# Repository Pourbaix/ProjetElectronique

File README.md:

# ProjetElectronique

## Description du projet

Ceci est le repository GitHub du projet d'électronique du groupe D

## Membres du groupe 

- BORKA Mark 
- GEONET Antoine
- NECHIFOR Bogdan
- POURBAIX Michaël
- DE SOUSA FEREIRA Nuno

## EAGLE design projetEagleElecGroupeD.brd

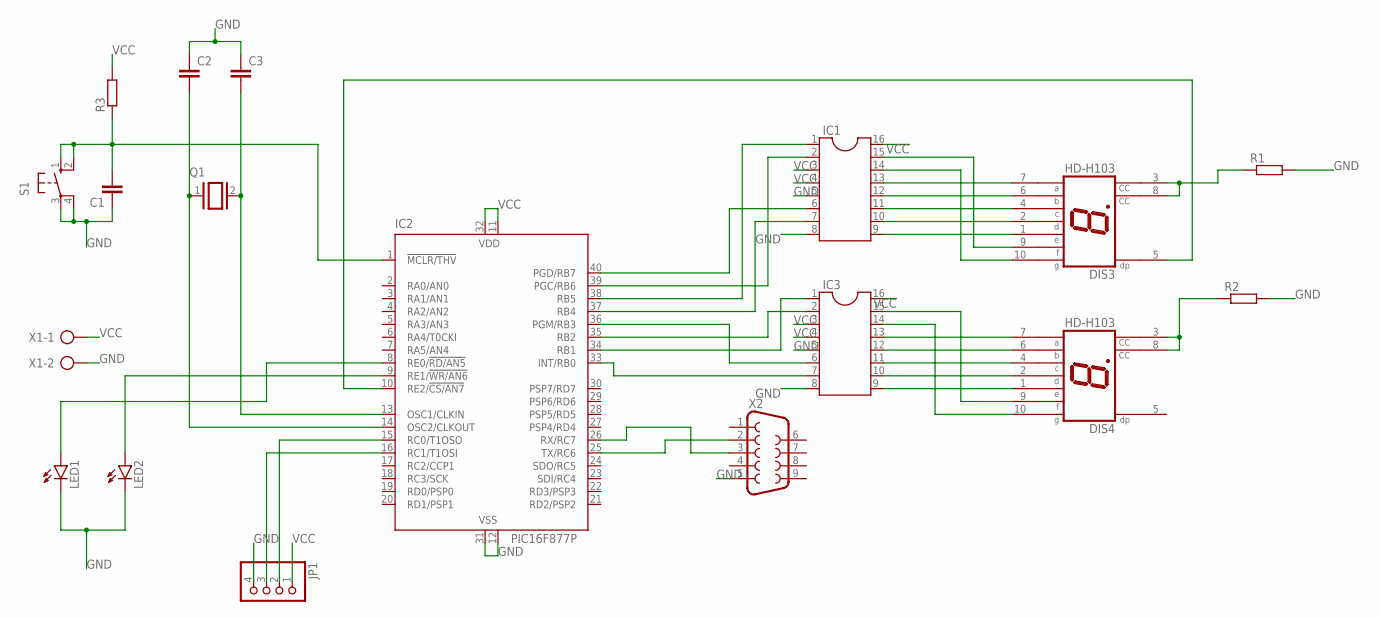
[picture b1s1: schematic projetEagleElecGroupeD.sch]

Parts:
C1, C2, C3: C-EU025-025X050; C025-025X050
DIS3, DIS4: HD-H103; HDSP-M
IC1, IC3: DIL16
IC2: PIC16F877P; DIL40
JP1: PINHD-1X4; 1X04
LED1, LED2: LED5MM
Q1: XTAL/S; QS
R1, R2, R3: R-EU_0207/10; 0207/10
S1: 10-XX; B3F-10XX
X1: AK300/2
X2: F09H

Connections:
GND: C1.1, C2.1, C3.1, IC1.5, IC1.8, IC2.12 (VSS), IC2.31 (VSS), IC3.5, IC3.8, JP1.4, LED1.K (C), LED2.K (C), R1.2, R2.2, S1.3, S1.4 (P1), X1.2, X2.5
unnamed: IC2.25 (TX/RC6), X2.2
unnamed: IC2.26 (RX/RC7), X2.3
unnamed: IC1.7, IC2.37 (RB4)
unnamed: IC1.1, IC2.38 (RB5)
unnamed: IC1.2, IC2.39 (PGC/RB6)
unnamed: IC1.6, IC2.40 (PGD/RB7)
unnamed: IC2.33 (INT/RB0), IC3.7
unnamed: IC2.34 (RB1), IC3.1
unnamed: IC2.35 (RB2), IC3.2
unnamed: IC2.36 (PGM/RB3), IC3.6
unnamed: DIS3.5 (DP), IC2.10 (RE2/!CS/AN7)
unnamed: C1.2, IC2.1 (!MCLR/THV), R3.1, S1.1 (S), S1.2 (S1)
unnamed: DIS4.3 (CC), DIS4.8 (CC), R2.1
unnamed: C3.2, IC2.13 (OSC1/CLKIN), Q1.2
unnamed: C2.2, IC2.14 (OSC2/CLKOUT), Q1.1
unnamed: DIS3.3 (CC), DIS3.8 (CC), R1.1
unnamed: DIS3.7 (A), IC1.13
unnamed: DIS3.6 (B), IC1.12
unnamed: DIS3.4 (C), IC1.11
unnamed: DIS3.2 (D), IC1.10
unnamed: DIS3.1 (E), IC1.9
unnamed: DIS3.9 (F), IC1.15
unnamed: DIS3.10 (G), IC1.14
unnamed: DIS4.7 (A), IC3.13
unnamed: DIS4.6 (B), IC3.12
unnamed: DIS4.4 (C), IC3.11
unnamed: DIS4.2 (D), IC3.10
unnamed: DIS4.1 (E), IC3.9
unnamed: DIS4.9 (F), IC3.15
unnamed: DIS4.10 (G), IC3.14
unnamed: IC2.15 (RC0/T1OSO), JP1.2
unnamed: IC2.16 (RC1/T1OSI), JP1.3
unnamed: IC2.9 (RE1/!WR/AN6), LED2.A
unnamed: IC2.8 (RE0/!RD/AN5), LED1.A
VCC: IC1.3, IC1.4, IC1.16, IC2.11 (VDD), IC2.32 (VDD), IC3.3, IC3.4, IC3.16, JP1.1, R3.2, X1.1

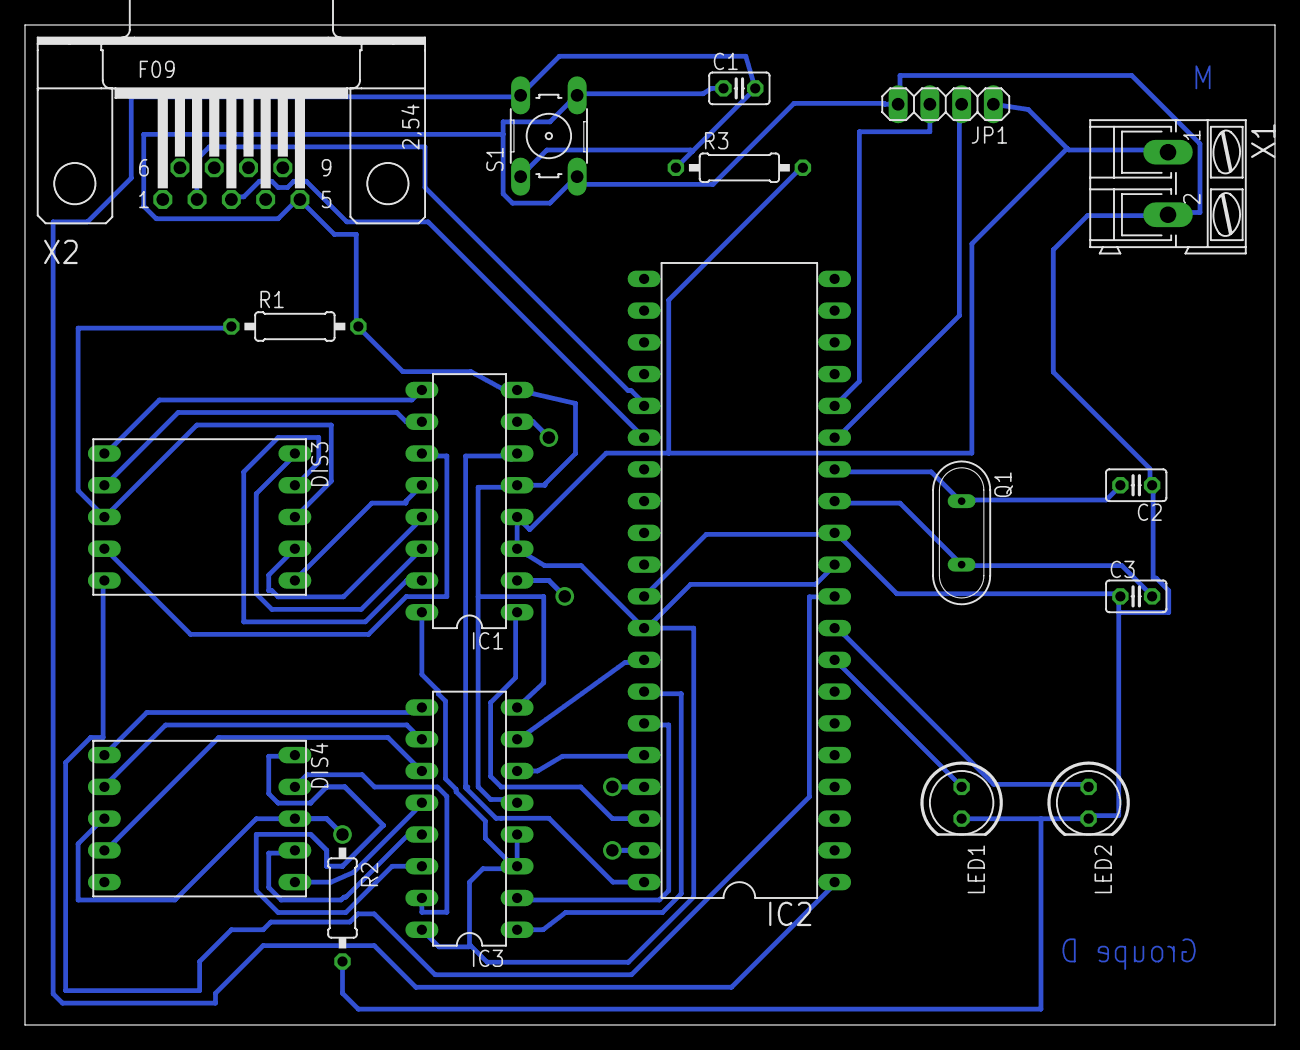
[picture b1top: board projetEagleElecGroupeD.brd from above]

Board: 2 copper layers, 100.0 x 80.0 mm, 18 parts (0 on the bottom side), 36 nets.

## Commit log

2022-03-29 Adding schematic files (proteus and eagle)
